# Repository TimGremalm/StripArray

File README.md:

# StripArray
A addressable RGB LED strip array driver based on WS2811 and IRLML6344 N-fet.

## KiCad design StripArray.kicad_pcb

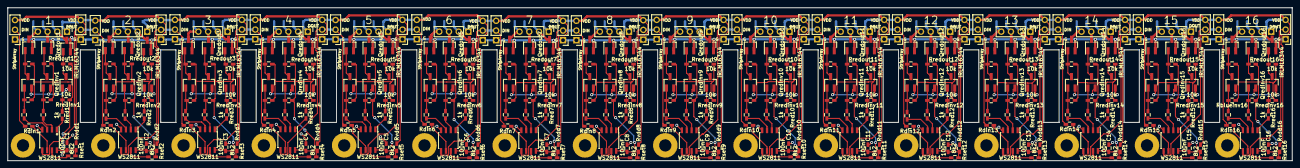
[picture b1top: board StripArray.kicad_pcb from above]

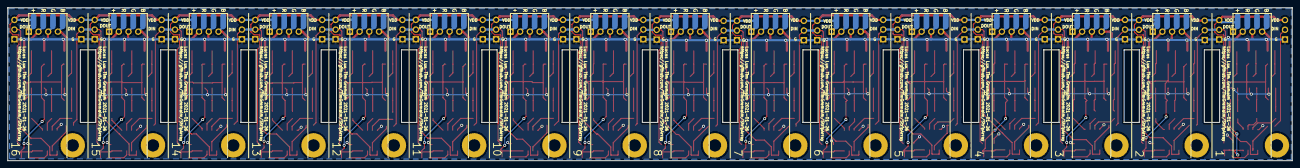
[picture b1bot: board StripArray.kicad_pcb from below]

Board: 2 copper layers, 336.0 x 40.0 mm, 400 parts (16 on the bottom side), 259 nets.

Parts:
C1, C2, C3, C4, C5, C6, C7, C8, C9, C10, C11, C12, C13, C14, C15, C16: 100nF; C_0603_HandSoldering
Hbottomleft1, Hbottomleft2, Hbottomleft3, Hbottomleft4, Hbottomleft5, Hbottomleft6, Hbottomleft7, Hbottomleft8, Hbottomleft9, Hbottomleft10, Hbottomleft11, Hbottomleft12, Hbottomleft13, Hbottomleft14, Hbottomleft15, Hbottomleft16: MountingHole; MountingHole_3.2mm_M3_Pad
Jin1, Jin2, Jin3, Jin4, Jin5, Jin6, Jin7, Jin8, Jin9, Jin10, Jin11, Jin12, Jin13, Jin14, Jin15, Jin16: Conn_01x03; Pin_Header_Straight_1x03_Pitch2.54mm
Jout1, Jout2, Jout3, Jout4, Jout5, Jout6, Jout7, Jout8, Jout9, Jout10, Jout11, Jout12, Jout13, Jout14, Jout15, Jout16: Conn_01x03; Pin_Header_Straight_1x03_Pitch2.54mm
Jrgb1, Jrgb2, Jrgb3, Jrgb4, Jrgb5, Jrgb6, Jrgb7, Jrgb8, Jrgb9, Jrgb10, Jrgb11, Jrgb12, Jrgb13, Jrgb14, Jrgb15, Jrgb16: Conn_01x04_Female; Pin_Header_Straight_1x04_Pitch2.54mm
LedStrip1, LedStrip2, LedStrip3, LedStrip4, LedStrip5, LedStrip6, LedStrip7, LedStrip8, LedStrip9, LedStrip10, LedStrip11, LedStrip12, LedStrip13, LedStrip14, LedStrip15, LedStrip16: Conn_01x04; RGB_Strip
Qblueinv1, Qblueinv2, Qblueinv3, Qblueinv4, Qblueinv5, Qblueinv6, Qblueinv7, Qblueinv8, Qblueinv9, Qblueinv10, Qblueinv11, Qblueinv12, Qblueinv13, Qblueinv14, Qblueinv15, Qblueinv16: IRLML6344; SOT-23_Handsoldering
Qblueout1, Qblueout2, Qblueout3, Qblueout4, Qblueout5, Qblueout6, Qblueout7, Qblueout8, Qblueout9, Qblueout10, Qblueout11, Qblueout12, Qblueout13, Qblueout14, Qblueout15, Qblueout16: IRLML6344; SOT-23_Handsoldering
Qgreeninv1, Qgreeninv2, Qgreeninv3, Qgreeninv4, Qgreeninv5, Qgreeninv6, Qgreeninv7, Qgreeninv8, Qgreeninv9, Qgreeninv10, Qgreeninv11, Qgreeninv12, Qgreeninv13, Qgreeninv14, Qgreeninv15, Qgreeninv16: IRLML6344; SOT-23_Handsoldering
Qgreenout1, Qgreenout2, Qgreenout3, Qgreenout4, Qgreenout5, Qgreenout6, Qgreenout7, Qgreenout8, Qgreenout9, Qgreenout10, Qgreenout11, Qgreenout12, Qgreenout13, Qgreenout14, Qgreenout15, Qgreenout16: IRLML6344; SOT-23_Handsoldering
Qredinv1, Qredinv2, Qredinv3, Qredinv4, Qredinv5, Qredinv6, Qredinv7, Qredinv8, Qredinv9, Qredinv10, Qredinv11, Qredinv12, Qredinv13, Qredinv14, Qredinv15, Qredinv16: IRLML6344; SOT-23_Handsoldering
Qredout1, Qredout2, Qredout3, Qredout4, Qredout5, Qredout6, Qredout7, Qredout8, Qredout9, Qredout10, Qredout11, Qredout12, Qredout13, Qredout14, Qredout15, Qredout16: IRLML6344; SOT-23_Handsoldering
Rblue1, Rblue2, Rblue3, Rblue4, Rblue5, Rblue6, Rblue7, Rblue8, Rblue9, Rblue10, Rblue11, Rblue12, Rblue13, Rblue14, Rblue15, Rblue16: 1k; C_0603_HandSoldering
Rblueinv1, Rblueinv2, Rblueinv3, Rblueinv4, Rblueinv5, Rblueinv6, Rblueinv7, Rblueinv8, Rblueinv9, Rblueinv10, Rblueinv11, Rblueinv12, Rblueinv13, Rblueinv14, Rblueinv15, Rblueinv16: 10k; C_0603_HandSoldering
Rblueout1, Rblueout2, Rblueout3, Rblueout4, Rblueout5, Rblueout6, Rblueout7, Rblueout8, Rblueout9, Rblueout10, Rblueout11, Rblueout12, Rblueout13, Rblueout14, Rblueout15, Rblueout16: 10k; C_0603_HandSoldering
Rdin1, Rdin2, Rdin3, Rdin4, Rdin5, Rdin6, Rdin7, Rdin8, Rdin9, Rdin10, Rdin11, Rdin12, Rdin13, Rdin14, Rdin15, Rdin16: 33R; C_0603_HandSoldering
Rgreen1, Rgreen2, Rgreen3, Rgreen4, Rgreen5, Rgreen6, Rgreen7, Rgreen8, Rgreen9, Rgreen10, Rgreen11, Rgreen12, Rgreen13, Rgreen14, Rgreen15, Rgreen16: 1k; C_0603_HandSoldering
Rgreeninv1, Rgreeninv2, Rgreeninv3, Rgreeninv4, Rgreeninv5, Rgreeninv6, Rgreeninv7, Rgreeninv8, Rgreeninv9, Rgreeninv10, Rgreeninv11, Rgreeninv12, Rgreeninv13, Rgreeninv14, Rgreeninv15, Rgreeninv16: 10k; C_0603_HandSoldering
Rgreenout1, Rgreenout2, Rgreenout3, Rgreenout4, Rgreenout5, Rgreenout6, Rgreenout7, Rgreenout8, Rgreenout9, Rgreenout10, Rgreenout11, Rgreenout12, Rgreenout13, Rgreenout14, Rgreenout15, Rgreenout16: 10k; C_0603_HandSoldering
Rred1, Rred2, Rred3, Rred4, Rred5, Rred6, Rred7, Rred8, Rred9, Rred10, Rred11, Rred12, Rred13, Rred14, Rred15, Rred16: 1k; C_0603_HandSoldering
Rredinv1, Rredinv2, Rredinv3, Rredinv4, Rredinv5, Rredinv6, Rredinv7, Rredinv8, Rredinv9, Rredinv10, Rredinv11, Rredinv12, Rredinv13, Rredinv14, Rredinv15, Rredinv16: 10k; C_0603_HandSoldering
Rredout1, Rredout2, Rredout3, Rredout4, Rredout5, Rredout6, Rredout7, Rredout8, Rredout9, Rredout10, Rredout11, Rredout12, Rredout13, Rredout14, Rredout15, Rredout16: 10k; C_0603_HandSoldering
Rset1, Rset2, Rset3, Rset4, Rset5, Rset6, Rset7, Rset8, Rset9, Rset10, Rset11, Rset12, Rset13, Rset14, Rset15, Rset16: 0R; C_0603_HandSoldering
Rvdd1, Rvdd2, Rvdd3, Rvdd4, Rvdd5, Rvdd6, Rvdd7, Rvdd8, Rvdd9, Rvdd10, Rvdd11, Rvdd12, Rvdd13, Rvdd14, Rvdd15, Rvdd16: 8k2; C_0603_HandSoldering
U1, U2, U3, U4, U5, U6, U7, U8, U9, U10, U11, U12, U13, U14, U15, U16: WS2811; SOIC-8_3.9x4.9mm_Pitch1.27mm

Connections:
/AddressableLedDriver01/DIN: Jin1.2, Rdin1.2
/AddressableLedDriver01/GndIn: C1.2, C2.2, C3.2, C4.2, C5.2, C6.2, C7.2, C8.2, C9.2, C10.2, C11.2, C12.2, C13.2, C14.2, C15.2, C16.2, Jin1.1, Jin2.1, Jin3.1, Jin4.1, Jin5.1, Jin6.1, Jin7.1, Jin8.1, Jin9.1, Jin10.1, Jin11.1, Jin12.1, Jin13.1, Jin14.1, Jin15.1, Jin16.1, Jout1.1, Jout2.1, Jout3.1, Jout4.1, Jout5.1, Jout6.1, Jout7.1, Jout8.1, Jout9.1, Jout10.1, Jout11.1, Jout12.1, Jout13.1, Jout14.1, Jout15.1, Jout16.1, Qblueinv1.2, Qblueinv2.2, Qblueinv3.2, Qblueinv4.2, Qblueinv5.2, Qblueinv6.2, Qblueinv7.2, Qblueinv8.2, Qblueinv9.2, Qblueinv10.2, Qblueinv11.2, Qblueinv12.2, Qblueinv13.2, Qblueinv14.2, Qblueinv15.2, Qblueinv16.2, Qblueout1.2, Qblueout2.2, Qblueout3.2, Qblueout4.2, Qblueout5.2, Qblueout6.2, Qblueout7.2, Qblueout8.2, Qblueout9.2, Qblueout10.2, Qblueout11.2, Qblueout12.2, Qblueout13.2, Qblueout14.2, Qblueout15.2, Qblueout16.2, Qgreeninv1.2, Qgreeninv2.2, Qgreeninv3.2, Qgreeninv4.2, Qgreeninv5.2, Qgreeninv6.2, Qgreeninv7.2, Qgreeninv8.2, Qgreeninv9.2, Qgreeninv10.2, Qgreeninv11.2, Qgreeninv12.2, Qgreeninv13.2, Qgreeninv14.2, Qgreeninv15.2, Qgreeninv16.2, Qgreenout1.2, Qgreenout2.2, Qgreenout3.2, Qgreenout4.2, Qgreenout5.2, Qgreenout6.2, Qgreenout7.2, Qgreenout8.2, Qgreenout9.2, Qgreenout10.2, Qgreenout11.2, Qgreenout12.2, Qgreenout13.2, Qgreenout14.2, Qgreenout15.2, Qgreenout16.2, Qredinv1.2, Qredinv2.2, Qredinv3.2, Qredinv4.2, Qredinv5.2, Qredinv6.2, Qredinv7.2, Qredinv8.2, Qredinv9.2, Qredinv10.2, Qredinv11.2, Qredinv12.2, Qredinv13.2, Qredinv14.2, Qredinv15.2, Qredinv16.2, Qredout1.2, Qredout2.2, Qredout3.2, Qredout4.2, Qredout5.2, Qredout6.2, Qredout7.2, Qredout8.2, Qredout9.2, Qredout10.2, Qredout11.2, Qredout12.2, Qredout13.2, Qredout14.2, Qredout15.2, Qredout16.2, U1.4, U2.4, U3.4, U4.4, U5.4, U6.4, U7.4, U8.4, U9.4, U10.4, U11.4, U12.4, U13.4, U14.4, U15.4, U16.4
/AddressableLedDriver01/VIn: Jin1.3, Jin2.3, Jin3.3, Jin4.3, Jin5.3, Jin6.3, Jin7.3, Jin8.3, Jin9.3, Jin10.3, Jin11.3, Jin12.3, Jin13.3, Jin14.3, Jin15.3, Jin16.3, Jout1.3, Jout2.3, Jout3.3, Jout4.3, Jout5.3, Jout6.3, Jout7.3, Jout8.3, Jout9.3, Jout10.3, Jout11.3, Jout12.3, Jout13.3, Jout14.3, Jout15.3, Jout16.3, Jrgb1.1, Jrgb2.1, Jrgb3.1, Jrgb4.1, Jrgb5.1, Jrgb6.1, Jrgb7.1, Jrgb8.1, Jrgb9.1, Jrgb10.1, Jrgb11.1, Jrgb12.1, Jrgb13.1, Jrgb14.1, Jrgb15.1, Jrgb16.1, LedStrip1.1, LedStrip2.1, LedStrip3.1, LedStrip4.1, LedStrip5.1, LedStrip6.1, LedStrip7.1, LedStrip8.1, LedStrip9.1, LedStrip10.1, LedStrip11.1, LedStrip12.1, LedStrip13.1, LedStrip14.1, LedStrip15.1, LedStrip16.1, Rvdd1.1, Rvdd2.1, Rvdd3.1, Rvdd4.1, Rvdd5.1, Rvdd6.1, Rvdd7.1, Rvdd8.1, Rvdd9.1, Rvdd10.1, Rvdd11.1, Rvdd12.1, Rvdd13.1, Rvdd14.1, Rvdd15.1, Rvdd16.1
/AddressableLedDriver02/DIN: Jin2.2, Jout1.2, Rdin2.2, U1.5
/AddressableLedDriver03/DIN: Jin3.2, Jout2.2, Rdin3.2, U2.5
/AddressableLedDriver04/DIN: Jin4.2, Jout3.2, Rdin4.2, U3.5
/AddressableLedDriver05/DIN: Jin5.2, Jout4.2, Rdin5.2, U4.5
/AddressableLedDriver06/DIN: Jin6.2, Jout5.2, Rdin6.2, U5.5
/AddressableLedDriver07/DIN: Jin7.2, Jout6.2, Rdin7.2, U6.5
/AddressableLedDriver08/DIN: Jin8.2, Jout7.2, Rdin8.2, U7.5
/AddressableLedDriver09/DIN: Jin9.2, Jout8.2, Rdin9.2, U8.5
/AddressableLedDriver10/DIN: Jin10.2, Jout9.2, Rdin10.2, U9.5
/AddressableLedDriver11/DIN: Jin11.2, Jout10.2, Rdin11.2, U10.5
/AddressableLedDriver12/DIN: Jin12.2, Jout11.2, Rdin12.2, U11.5
/AddressableLedDriver13/DIN: Jin13.2, Jout12.2, Rdin13.2, U12.5
/AddressableLedDriver14/DIN: Jin14.2, Jout13.2, Rdin14.2, U13.5
/AddressableLedDriver15/DIN: Jin15.2, Jout14.2, Rdin15.2, U14.5
/AddressableLedDriver16/DIN: Jin16.2, Jout15.2, Rdin16.2, U15.5
/AddressableLedDriver16/DOUT: Jout16.2, U16.5
unnamed: C1.1, Rblueinv1.1, Rblueout1.1, Rgreeninv1.1, Rgreenout1.1, Rredinv1.1, Rredout1.1, Rset1.1, Rvdd1.2, U1.8
unnamed: C2.1, Rblueinv2.1, Rblueout2.1, Rgreeninv2.1, Rgreenout2.1, Rredinv2.1, Rredout2.1, Rset2.1, Rvdd2.2, U2.8
unnamed: C3.1, Rblueinv3.1, Rblueout3.1, Rgreeninv3.1, Rgreenout3.1, Rredinv3.1, Rredout3.1, Rset3.1, Rvdd3.2, U3.8
unnamed: C4.1, Rblueinv4.1, Rblueout4.1, Rgreeninv4.1, Rgreenout4.1, Rredinv4.1, Rredout4.1, Rset4.1, Rvdd4.2, U4.8
unnamed: C5.1, Rblueinv5.1, Rblueout5.1, Rgreeninv5.1, Rgreenout5.1, Rredinv5.1, Rredout5.1, Rset5.1, Rvdd5.2, U5.8
unnamed: C6.1, Rblueinv6.1, Rblueout6.1, Rgreeninv6.1, Rgreenout6.1, Rredinv6.1, Rredout6.1, Rset6.1, Rvdd6.2, U6.8
unnamed: C7.1, Rblueinv7.1, Rblueout7.1, Rgreeninv7.1, Rgreenout7.1, Rredinv7.1, Rredout7.1, Rset7.1, Rvdd7.2, U7.8
unnamed: C8.1, Rblueinv8.1, Rblueout8.1, Rgreeninv8.1, Rgreenout8.1, Rredinv8.1, Rredout8.1, Rset8.1, Rvdd8.2, U8.8
unnamed: C9.1, Rblueinv9.1, Rblueout9.1, Rgreeninv9.1, Rgreenout9.1, Rredinv9.1, Rredout9.1, Rset9.1, Rvdd9.2, U9.8
unnamed: C10.1, Rblueinv10.1, Rblueout10.1, Rgreeninv10.1, Rgreenout10.1, Rredinv10.1, Rredout10.1, Rset10.1, Rvdd10.2, U10.8
unnamed: C11.1, Rblueinv11.1, Rblueout11.1, Rgreeninv11.1, Rgreenout11.1, Rredinv11.1, Rredout11.1, Rset11.1, Rvdd11.2, U11.8
unnamed: C12.1, Rblueinv12.1, Rblueout12.1, Rgreeninv12.1, Rgreenout12.1, Rredinv12.1, Rredout12.1, Rset12.1, Rvdd12.2, U12.8
unnamed: C13.1, Rblueinv13.1, Rblueout13.1, Rgreeninv13.1, Rgreenout13.1, Rredinv13.1, Rredout13.1, Rset13.1, Rvdd13.2, U13.8
unnamed: C14.1, Rblueinv14.1, Rblueout14.1, Rgreeninv14.1, Rgreenout14.1, Rredinv14.1, Rredout14.1, Rset14.1, Rvdd14.2, U14.8
unnamed: C15.1, Rblueinv15.1, Rblueout15.1, Rgreeninv15.1, Rgreenout15.1, Rredinv15.1, Rredout15.1, Rset15.1, Rvdd15.2, U15.8
unnamed: C16.1, Rblueinv16.1, Rblueout16.1, Rgreeninv16.1, Rgreenout16.1, Rredinv16.1, Rredout16.1, Rset16.1, Rvdd16.2, U16.8
unnamed: Jrgb1.2, LedStrip1.2, Qredout1.3
unnamed: Jrgb1.3, LedStrip1.3, Qgreenout1.3
unnamed: Jrgb1.4, LedStrip1.4, Qblueout1.3
unnamed: Jrgb2.2, LedStrip2.2, Qredout2.3
unnamed: Jrgb2.3, LedStrip2.3, Qgreenout2.3
unnamed: Jrgb2.4, LedStrip2.4, Qblueout2.3
unnamed: Jrgb3.2, LedStrip3.2, Qredout3.3
unnamed: Jrgb3.3, LedStrip3.3, Qgreenout3.3
unnamed: Jrgb3.4, LedStrip3.4, Qblueout3.3
unnamed: Jrgb4.2, LedStrip4.2, Qredout4.3
unnamed: Jrgb4.3, LedStrip4.3, Qgreenout4.3
unnamed: Jrgb4.4, LedStrip4.4, Qblueout4.3
unnamed: Jrgb5.2, LedStrip5.2, Qredout5.3
unnamed: Jrgb5.3, LedStrip5.3, Qgreenout5.3
unnamed: Jrgb5.4, LedStrip5.4, Qblueout5.3
unnamed: Jrgb6.2, LedStrip6.2, Qredout6.3
unnamed: Jrgb6.3, LedStrip6.3, Qgreenout6.3
unnamed: Jrgb6.4, LedStrip6.4, Qblueout6.3
unnamed: Jrgb7.2, LedStrip7.2, Qredout7.3
unnamed: Jrgb7.3, LedStrip7.3, Qgreenout7.3
unnamed: Jrgb7.4, LedStrip7.4, Qblueout7.3
unnamed: Jrgb8.2, LedStrip8.2, Qredout8.3
unnamed: Jrgb8.3, LedStrip8.3, Qgreenout8.3
unnamed: Jrgb8.4, LedStrip8.4, Qblueout8.3
unnamed: Jrgb9.2, LedStrip9.2, Qredout9.3
unnamed: Jrgb9.3, LedStrip9.3, Qgreenout9.3
unnamed: Jrgb9.4, LedStrip9.4, Qblueout9.3
unnamed: Jrgb10.2, LedStrip10.2, Qredout10.3
unnamed: Jrgb10.3, LedStrip10.3, Qgreenout10.3
unnamed: Jrgb10.4, LedStrip10.4, Qblueout10.3
unnamed: Jrgb11.2, LedStrip11.2, Qredout11.3
unnamed: Jrgb11.3, LedStrip11.3, Qgreenout11.3
unnamed: Jrgb11.4, LedStrip11.4, Qblueout11.3
unnamed: Jrgb12.2, LedStrip12.2, Qredout12.3
unnamed: Jrgb12.3, LedStrip12.3, Qgreenout12.3
unnamed: Jrgb12.4, LedStrip12.4, Qblueout12.3
unnamed: Jrgb13.2, LedStrip13.2, Qredout13.3
unnamed: Jrgb13.3, LedStrip13.3, Qgreenout13.3
unnamed: Jrgb13.4, LedStrip13.4, Qblueout13.3
unnamed: Jrgb14.2, LedStrip14.2, Qredout14.3
unnamed: Jrgb14.3, LedStrip14.3, Qgreenout14.3
unnamed: Jrgb14.4, LedStrip14.4, Qblueout14.3
unnamed: Jrgb15.2, LedStrip15.2, Qredout15.3
unnamed: Jrgb15.3, LedStrip15.3, Qgreenout15.3
unnamed: Jrgb15.4, LedStrip15.4, Qblueout15.3
unnamed: Jrgb16.2, LedStrip16.2, Qredout16.3
unnamed: Jrgb16.3, LedStrip16.3, Qgreenout16.3
unnamed: Jrgb16.4, LedStrip16.4, Qblueout16.3
unnamed: Qblueinv1.1, Rblue1.1, Rblueinv1.2
unnamed: Qblueinv1.3, Qblueout1.1, Rblueout1.2
unnamed: Qblueinv2.1, Rblue2.1, Rblueinv2.2
unnamed: Qblueinv2.3, Qblueout2.1, Rblueout2.2
unnamed: Qblueinv3.1, Rblue3.1, Rblueinv3.2
unnamed: Qblueinv3.3, Qblueout3.1, Rblueout3.2
unnamed: Qblueinv4.1, Rblue4.1, Rblueinv4.2
unnamed: Qblueinv4.3, Qblueout4.1, Rblueout4.2
unnamed: Qblueinv5.1, Rblue5.1, Rblueinv5.2
unnamed: Qblueinv5.3, Qblueout5.1, Rblueout5.2
unnamed: Qblueinv6.1, Rblue6.1, Rblueinv6.2
unnamed: Qblueinv6.3, Qblueout6.1, Rblueout6.2
unnamed: Qblueinv7.1, Rblue7.1, Rblueinv7.2
unnamed: Qblueinv7.3, Qblueout7.1, Rblueout7.2
unnamed: Qblueinv8.1, Rblue8.1, Rblueinv8.2
unnamed: Qblueinv8.3, Qblueout8.1, Rblueout8.2
unnamed: Qblueinv9.1, Rblue9.1, Rblueinv9.2
unnamed: Qblueinv9.3, Qblueout9.1, Rblueout9.2
unnamed: Qblueinv10.1, Rblue10.1, Rblueinv10.2
unnamed: Qblueinv10.3, Qblueout10.1, Rblueout10.2
unnamed: Qblueinv11.1, Rblue11.1, Rblueinv11.2
unnamed: Qblueinv11.3, Qblueout11.1, Rblueout11.2
unnamed: Qblueinv12.1, Rblue12.1, Rblueinv12.2
unnamed: Qblueinv12.3, Qblueout12.1, Rblueout12.2
unnamed: Qblueinv13.1, Rblue13.1, Rblueinv13.2
unnamed: Qblueinv13.3, Qblueout13.1, Rblueout13.2
unnamed: Qblueinv14.1, Rblue14.1, Rblueinv14.2
unnamed: Qblueinv14.3, Qblueout14.1, Rblueout14.2
unnamed: Qblueinv15.1, Rblue15.1, Rblueinv15.2
unnamed: Qblueinv15.3, Qblueout15.1, Rblueout15.2
unnamed: Qblueinv16.1, Rblue16.1, Rblueinv16.2
unnamed: Qblueinv16.3, Qblueout16.1, Rblueout16.2
unnamed: Qgreeninv1.1, Rgreen1.1, Rgreeninv1.2
unnamed: Qgreeninv1.3, Qgreenout1.1, Rgreenout1.2
unnamed: Qgreeninv2.1, Rgreen2.1, Rgreeninv2.2
unnamed: Qgreeninv2.3, Qgreenout2.1, Rgreenout2.2
unnamed: Qgreeninv3.1, Rgreen3.1, Rgreeninv3.2
unnamed: Qgreeninv3.3, Qgreenout3.1, Rgreenout3.2
unnamed: Qgreeninv4.1, Rgreen4.1, Rgreeninv4.2
unnamed: Qgreeninv4.3, Qgreenout4.1, Rgreenout4.2
unnamed: Qgreeninv5.1, Rgreen5.1, Rgreeninv5.2
unnamed: Qgreeninv5.3, Qgreenout5.1, Rgreenout5.2
unnamed: Qgreeninv6.1, Rgreen6.1, Rgreeninv6.2
unnamed: Qgreeninv6.3, Qgreenout6.1, Rgreenout6.2
unnamed: Qgreeninv7.1, Rgreen7.1, Rgreeninv7.2
unnamed: Qgreeninv7.3, Qgreenout7.1, Rgreenout7.2
unnamed: Qgreeninv8.1, Rgreen8.1, Rgreeninv8.2
unnamed: Qgreeninv8.3, Qgreenout8.1, Rgreenout8.2
unnamed: Qgreeninv9.1, Rgreen9.1, Rgreeninv9.2
unnamed: Qgreeninv9.3, Qgreenout9.1, Rgreenout9.2
unnamed: Qgreeninv10.1, Rgreen10.1, Rgreeninv10.2
unnamed: Qgreeninv10.3, Qgreenout10.1, Rgreenout10.2
unnamed: Qgreeninv11.1, Rgreen11.1, Rgreeninv11.2
unnamed: Qgreeninv11.3, Qgreenout11.1, Rgreenout11.2
unnamed: Qgreeninv12.1, Rgreen12.1, Rgreeninv12.2
unnamed: Qgreeninv12.3, Qgreenout12.1, Rgreenout12.2
unnamed: Qgreeninv13.1, Rgreen13.1, Rgreeninv13.2
unnamed: Qgreeninv13.3, Qgreenout13.1, Rgreenout13.2
unnamed: Qgreeninv14.1, Rgreen14.1, Rgreeninv14.2
unnamed: Qgreeninv14.3, Qgreenout14.1, Rgreenout14.2
unnamed: Qgreeninv15.1, Rgreen15.1, Rgreeninv15.2
unnamed: Qgreeninv15.3, Qgreenout15.1, Rgreenout15.2
unnamed: Qgreeninv16.1, Rgreen16.1, Rgreeninv16.2
unnamed: Qgreeninv16.3, Qgreenout16.1, Rgreenout16.2
unnamed: Qredinv1.1, Rred1.1, Rredinv1.2
unnamed: Qredinv1.3, Qredout1.1, Rredout1.2
unnamed: Qredinv2.1, Rred2.1, Rredinv2.2
unnamed: Qredinv2.3, Qredout2.1, Rredout2.2
unnamed: Qredinv3.1, Rred3.1, Rredinv3.2
unnamed: Qredinv3.3, Qredout3.1, Rredout3.2
unnamed: Qredinv4.1, Rred4.1, Rredinv4.2
unnamed: Qredinv4.3, Qredout4.1, Rredout4.2
unnamed: Qredinv5.1, Rred5.1, Rredinv5.2
unnamed: Qredinv5.3, Qredout5.1, Rredout5.2
unnamed: Qredinv6.1, Rred6.1, Rredinv6.2
unnamed: Qredinv6.3, Qredout6.1, Rredout6.2
unnamed: Qredinv7.1, Rred7.1, Rredinv7.2
unnamed: Qredinv7.3, Qredout7.1, Rredout7.2
unnamed: Qredinv8.1, Rred8.1, Rredinv8.2
unnamed: Qredinv8.3, Qredout8.1, Rredout8.2
unnamed: Qredinv9.1, Rred9.1, Rredinv9.2
unnamed: Qredinv9.3, Qredout9.1, Rredout9.2
unnamed: Qredinv10.1, Rred10.1, Rredinv10.2
unnamed: Qredinv10.3, Qredout10.1, Rredout10.2
unnamed: Qredinv11.1, Rred11.1, Rredinv11.2
unnamed: Qredinv11.3, Qredout11.1, Rredout11.2
unnamed: Qredinv12.1, Rred12.1, Rredinv12.2
unnamed: Qredinv12.3, Qredout12.1, Rredout12.2
unnamed: Qredinv13.1, Rred13.1, Rredinv13.2
unnamed: Qredinv13.3, Qredout13.1, Rredout13.2
unnamed: Qredinv14.1, Rred14.1, Rredinv14.2
unnamed: Qredinv14.3, Qredout14.1, Rredout14.2
unnamed: Qredinv15.1, Rred15.1, Rredinv15.2
unnamed: Qredinv15.3, Qredout15.1, Rredout15.2
unnamed: Qredinv16.1, Rred16.1, Rredinv16.2
unnamed: Qredinv16.3, Qredout16.1, Rredout16.2
unnamed: Rblue1.2, U1.3
unnamed: Rblue2.2, U2.3
unnamed: Rblue3.2, U3.3
unnamed: Rblue4.2, U4.3
unnamed: Rblue5.2, U5.3
unnamed: Rblue6.2, U6.3
unnamed: Rblue7.2, U7.3
unnamed: Rblue8.2, U8.3
unnamed: Rblue9.2, U9.3
unnamed: Rblue10.2, U10.3
unnamed: Rblue11.2, U11.3
unnamed: Rblue12.2, U12.3
unnamed: Rblue13.2, U13.3
unnamed: Rblue14.2, U14.3
unnamed: Rblue15.2, U15.3
unnamed: Rblue16.2, U16.3
unnamed: Rdin1.1, U1.6
unnamed: Rdin2.1, U2.6
unnamed: Rdin3.1, U3.6
unnamed: Rdin4.1, U4.6
unnamed: Rdin5.1, U5.6
unnamed: Rdin6.1, U6.6
unnamed: Rdin7.1, U7.6
unnamed: Rdin8.1, U8.6
unnamed: Rdin9.1, U9.6
unnamed: Rdin10.1, U10.6
unnamed: Rdin11.1, U11.6
unnamed: Rdin12.1, U12.6
unnamed: Rdin13.1, U13.6
unnamed: Rdin14.1, U14.6
unnamed: Rdin15.1, U15.6
unnamed: Rdin16.1, U16.6
unnamed: Rgreen1.2, U1.2
unnamed: Rgreen2.2, U2.2
unnamed: Rgreen3.2, U3.2
unnamed: Rgreen4.2, U4.2
unnamed: Rgreen5.2, U5.2
unnamed: Rgreen6.2, U6.2
unnamed: Rgreen7.2, U7.2
unnamed: Rgreen8.2, U8.2
unnamed: Rgreen9.2, U9.2
unnamed: Rgreen10.2, U10.2
unnamed: Rgreen11.2, U11.2
unnamed: Rgreen12.2, U12.2
unnamed: Rgreen13.2, U13.2
unnamed: Rgreen14.2, U14.2
unnamed: Rgreen15.2, U15.2
unnamed: Rgreen16.2, U16.2
unnamed: Rred1.2, U1.1
unnamed: Rred2.2, U2.1
unnamed: Rred3.2, U3.1
unnamed: Rred4.2, U4.1
unnamed: Rred5.2, U5.1
unnamed: Rred6.2, U6.1
unnamed: Rred7.2, U7.1
unnamed: Rred8.2, U8.1
unnamed: Rred9.2, U9.1
unnamed: Rred10.2, U10.1
unnamed: Rred11.2, U11.1
unnamed: Rred12.2, U12.1
unnamed: Rred13.2, U13.1
unnamed: Rred14.2, U14.1
unnamed: Rred15.2, U15.1
unnamed: Rred16.2, U16.1
unnamed: Rset1.2, U1.7
unnamed: Rset2.2, U2.7
unnamed: Rset3.2, U3.7
unnamed: Rset4.2, U4.7
unnamed: Rset5.2, U5.7
unnamed: Rset6.2, U6.7
unnamed: Rset7.2, U7.7
unnamed: Rset8.2, U8.7
unnamed: Rset9.2, U9.7
unnamed: Rset10.2, U10.7
unnamed: Rset11.2, U11.7
unnamed: Rset12.2, U12.7
unnamed: Rset13.2, U13.7
unnamed: Rset14.2, U14.7
unnamed: Rset15.2, U15.7
unnamed: Rset16.2, U16.7

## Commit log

2020-12-13 LED driver base
2021-01-15 Invert Output using extra fet stage
2021-01-16 RGB Strip footprint
2021-01-18 Added headers
2021-01-18 Led Driver addressable segment
2021-01-19 Restructure schema
2021-01-19 Add array of LED Driver
2021-01-19 Add footprint to mosfets
2021-01-19 Change Led Strip footprint to RGB
2021-01-20 Removed faulty junction between DIN and GND
2021-01-20 PCB layout of LED Driver
2021-01-20 LED Driver array PCB
2021-01-20 Draw borders in silk on PCB
2021-01-21 Add logotype to silk
2021-01-22 PCB routing
2021-01-22 Continued PCB routing
2021-01-23 Comment schematic, titles
2021-01-23 Resistor for WS2811 set pin 400/800kHz
2021-01-23 Add extra RGB header
2021-01-24 Route new headers
2021-01-24 Add logotype
2021-01-25 Update silk desc
2021-01-26 Add design to silk
2021-01-26 Gerbers and PDF Schema
2021-01-26 Add interactive BOM and DNP fields to headers
2021-01-26 Minor edits
